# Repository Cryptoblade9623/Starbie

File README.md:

# Starbie
Motion and button controlled pet with an OLED display, humidity and temperature sensor and motion sensor.
It is controlled by an ESP32 C3 Supermini.
This is a guide, by SharKing Studios from Half-Life.
The files include the KiCad files, gerbers, drill files, firmware - which you will have to put into a folder of the same name and then open in the Arduino IDE, footprints for the custom silkscreen, non - KiCad symbols and footprints for the screen, ESP32, and DHT11, and my personal sprite creation.
I have not included the swicthes and keycaps because I have 4 switches and quite a few keycaps from previous projects.

## Instructions
1. Solder the 10K ohm resistor onto the top left corner of the board.
2. Solder the MPU6050 onto the middle area of the board with pinheaders.
3. Solder the mechanical switches into their corners on the PCB.
4. Solder on the OLED display in the middle of the board, above the MPU6050.
5. Solder the DHT11 in between the resistor and the OLED.
6. Finally solder the ESP32 onto the right side of the board so that the USBC port just hangs off the egde.
7. You can also add some small stickers onto the tips of the corners or on the back if you have them, but this is completely optional.
And you're done!

## BOM
| Name                | Purpose                                                                 | Quantity | Price | Total | Vendor     | Link                                                                                                                                                                                                                                                                                                                                                                                                                                                                                                                                                                                                                                                                                                |
|---------------------|-------------------------------------------------------------------------|----------|-------|-------|------------|-----------------------------------------------------------------------------------------------------------------------------------------------------------------------------------------------------------------------------------------------------------------------------------------------------------------------------------------------------------------------------------------------------------------------------------------------------------------------------------------------------------------------------------------------------------------------------------------------------------------------------------------------------------------------------------------------------|
| ESP32 C3 Supermini  | Control the screen and take inputs from the other parts.                | 1        | $3.05 | $3.05 | AliExpress | https://www.aliexpress.com/item/1005007869446657.html?spm=a2g0o.productlist.main.11.206e1bcdmjCEWO&algo_pvid=0b73490b-3db1-475a-b949-48b70c4bc669&algo_exp_id=0b73490b-3db1-475a-b949-48b70c4bc669-10&pdp_ext_f=%7B%22order%22%3A%22625%22%2C%22eval%22%3A%221%22%2C%22fromPage%22%3A%22search%22%7D&pdp_npi=6%40dis%21USD%213.05%211.35%21%21%213.05%211.35%21%4021038a9c17917201267658074e0e1e%2112000042625562850%21sea%21GB%210%21ABX%211%210%21n_tag%3A-29910%3Bd%3Ad6cd2d24%3Bm03_new_user%3A-29895%3BpisId%3A5000000218643706&curPageLogUid=5fYpmBZWpQCx&utparam-url=scene%3Asearch%7Cquery_from%3A%7Cx_object_id%3A1005007869446657%7C_p_origin_prod%3A                                     |
| MPU6050             | Measure when and how far the starbie moves, and the temperature.        | 1        | $6.35 | $6.35 | AliExpress | https://www.aliexpress.com/item/1005009301512511.html?spm=a2g0o.productlist.main.6.48303357KSQoac&algo_pvid=a6a14264-ed01-42b3-9622-6b7e0ab05deb&algo_exp_id=a6a14264-ed01-42b3-9622-6b7e0ab05deb-5&pdp_ext_f=%7B%22order%22%3A%22896%22%2C%22eval%22%3A%221%22%2C%22fromPage%22%3A%22search%22%7D&pdp_npi=6%40dis%21USD%216.35%211.35%21%21%2142.31%218.97%21%4021038efe17917202091956114e0e9d%2112000048670005993%21sea%21GB%210%21ABX%211%210%21n_tag%3A-29910%3Bd%3Ad6cd2d24%3Bm03_new_user%3A-29895%3BpisId%3A5000000218643719&curPageLogUid=6Pyg4t6bDySC&utparam-url=scene%3Asearch%7Cquery_from%3A%7Cx_object_id%3A1005009301512511%7C_p_origin_prod%3A                                      |
| DHT11               | Measures temperature and humidity.                                      | 1        | $1.33 | $1.33 | AliExpress | https://www.aliexpress.com/item/1005008139877691.html?spm=a2g0o.productlist.main.56.478071f3PHmWQL&algo_pvid=b0108e3c-d75b-4ddc-9645-f7381e120316&algo_exp_id=b0108e3c-d75b-4ddc-9645-f7381e120316-53&pdp_ext_f=%7B%22order%22%3A%2248%22%2C%22spu_best_type%22%3A%22price%22%2C%22eval%22%3A%221%22%2C%22fromPage%22%3A%22search%22%7D&pdp_npi=6%40dis%21USD%212.94%211.46%21%21%2119.61%219.73%21%400b0fe0e117917203029507771e0fae%2112000043957898813%21sea%21GB%210%21ABX%211%210%21n_tag%3A-29910%3Bd%3Ad6cd2d24%3Bm03_new_user%3A-29895%3BpisId%3A5000000218644952&curPageLogUid=Pg4XL4u82SU3&utparam-url=scene%3Asearch%7Cquery_from%3A%7Cx_object_id%3A1005008139877691%7C_p_origin_prod%3A |
| 0.96"" OLED Display | Show the user the character, special effects, humidity and temperature. | 1        | $2.69 | $2.69 | AliExpress | https://www.aliexpress.com/item/1005005462085489.html?spm=a2g0o.productlist.main.2.322d89ddrd7TtE&algo_pvid=498f8125-b214-45ec-ab85-9c8a85e03899&algo_exp_id=498f8125-b214-45ec-ab85-9c8a85e03899-1&pdp_ext_f=%7B%22order%22%3A%22452%22%2C%22spu_best_type%22%3A%22price%22%2C%22eval%22%3A%221%22%2C%22fromPage%22%3A%22search%22%7D&pdp_npi=6%40dis%21USD%212.69%211.35%21%21%212.69%211.35%21%4021613b2717917205198501835e102d%2112000049496537372%21sea%21GB%210%21ABX%211%210%21n_tag%3A-29910%3Bd%3Ad6cd2d24%3Bm03_new_user%3A-29895%3BpisId%3A5000000218643705&curPageLogUid=lBeDxeLcDOXl&utparam-url=scene%3Asearch%7Cquery_from%3A%7Cx_object_id%3A1005005462085489%7C_p_origin_prod%3A   |
| 10K? Resistor       | Limit the power going to the DHT11.                                     | 1        | $0.48 | $0.48 | AliExpress | https://www.aliexpress.com/item/1005004268846582.html?spm=a2g0o.productlist.main.11.7c462a0aVNMxSC&algo_pvid=5fe0ab05-7f95-40c5-b6f9-e457673b242f&algo_exp_id=5fe0ab05-7f95-40c5-b6f9-e457673b242f-40&pdp_ext_f=%7B%22order%22%3A%22228%22%2C%22eval%22%3A%221%22%2C%22fromPage%22%3A%22search%22%7D&pdp_npi=6%40dis%21USD%210.48%210.48%21%21%210.48%210.48%21%402103849717917384362504889e0ecf%2112000028578601225%21sea%21GB%210%21ABX%211%210%21n_tag%3A-29910%3Bd%3Ad6cd2d24%3Bm03_new_user%3A-29895&curPageLogUid=vm2vWDKw8xaz&utparam-url=scene%3Asearch%7Cquery_from%3A%7Cx_object_id%3A1005004268846582%7C_p_origin_prod%3A                                                                |
| PCB                 | Connect everything and hold it together (Min. 5).                       | 5        | $0.80 | $4.00 | JLCPCB     | https://cart.jlcpcb.com/shopcart/cart/                                                                                                                                                                                                                                                                                                                                                                                                                                                                                                                                                                                                                                                              |
|                     |                                                                         |          |       |       |            |                                                                                                                                                                                                                                                                                                                                                                                                                                                                                                                                                                                                                                                                                                     |
| Subtotal            | $17.90                                                                  |          |       |       |            |                                                                                                                                                                                                                                                                                                                                                                                                                                                                                                                                                                                                                                                                                                     |
| Taxes & Shipping    | $9.28                                                                   |          |       |       |            |                                                                                                                                                                                                                                                                                                                                                                                                                                                                                                                                                                                                                                                                                                     |
| Grand Total         | $27.18                                                                  |          |       |       |            |                                                                                                                                                                                                                                                                                                                                                                                                                                                                                                                                                                                                                                                                                                     |

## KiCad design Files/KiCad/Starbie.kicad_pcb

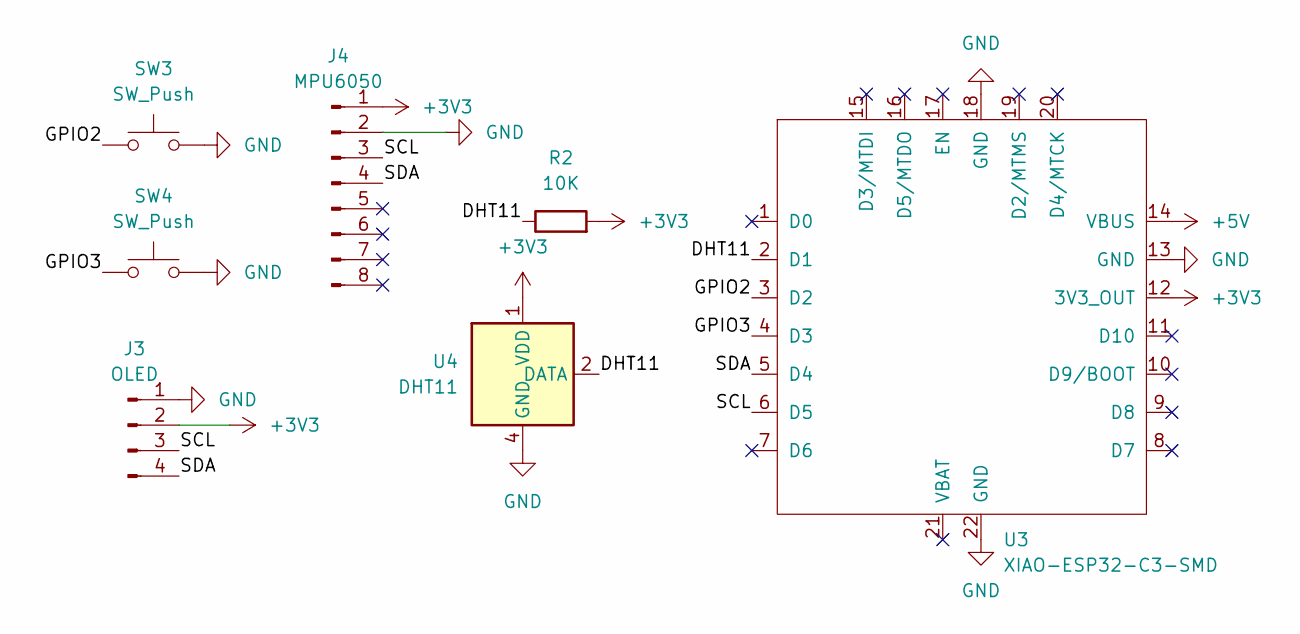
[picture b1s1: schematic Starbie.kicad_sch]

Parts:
J3: OLED; Display_128x64_096_I2C
J4: MPU6050; MPU6050_Module
R2: 10K; R_Axial_DIN0204_L3.6mm_D1.6mm_P7.62mm_Horizontal
SW3, SW4: SW_Push; SW_Cherry_MX_1.00u_PCB
U3: XIAO-ESP32-C3-SMD
U4: DHT11; Aosong_DHT11_5.5x12.0_P2.54mm

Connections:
+3V3: J3.2, J4.1, R2.2, U3.12 (3V3_OUT), U4.1 (VDD)
+5V: U3.14 (VBUS)
/DHT11: R2.1, U3.2 (D1), U4.2 (DATA)
/GPIO2: SW3.1, U3.3 (D2)
/GPIO3: SW4.1, U3.4 (D3)
/SCL: J3.3, J4.3, U3.6 (D5)
/SDA: J3.4, J4.4, U3.5 (D4)
GND: J3.1, J4.2, SW3.2, SW4.2, U3.13 (GND), U3.18 (GND), U3.22 (GND), U4.4 (GND)

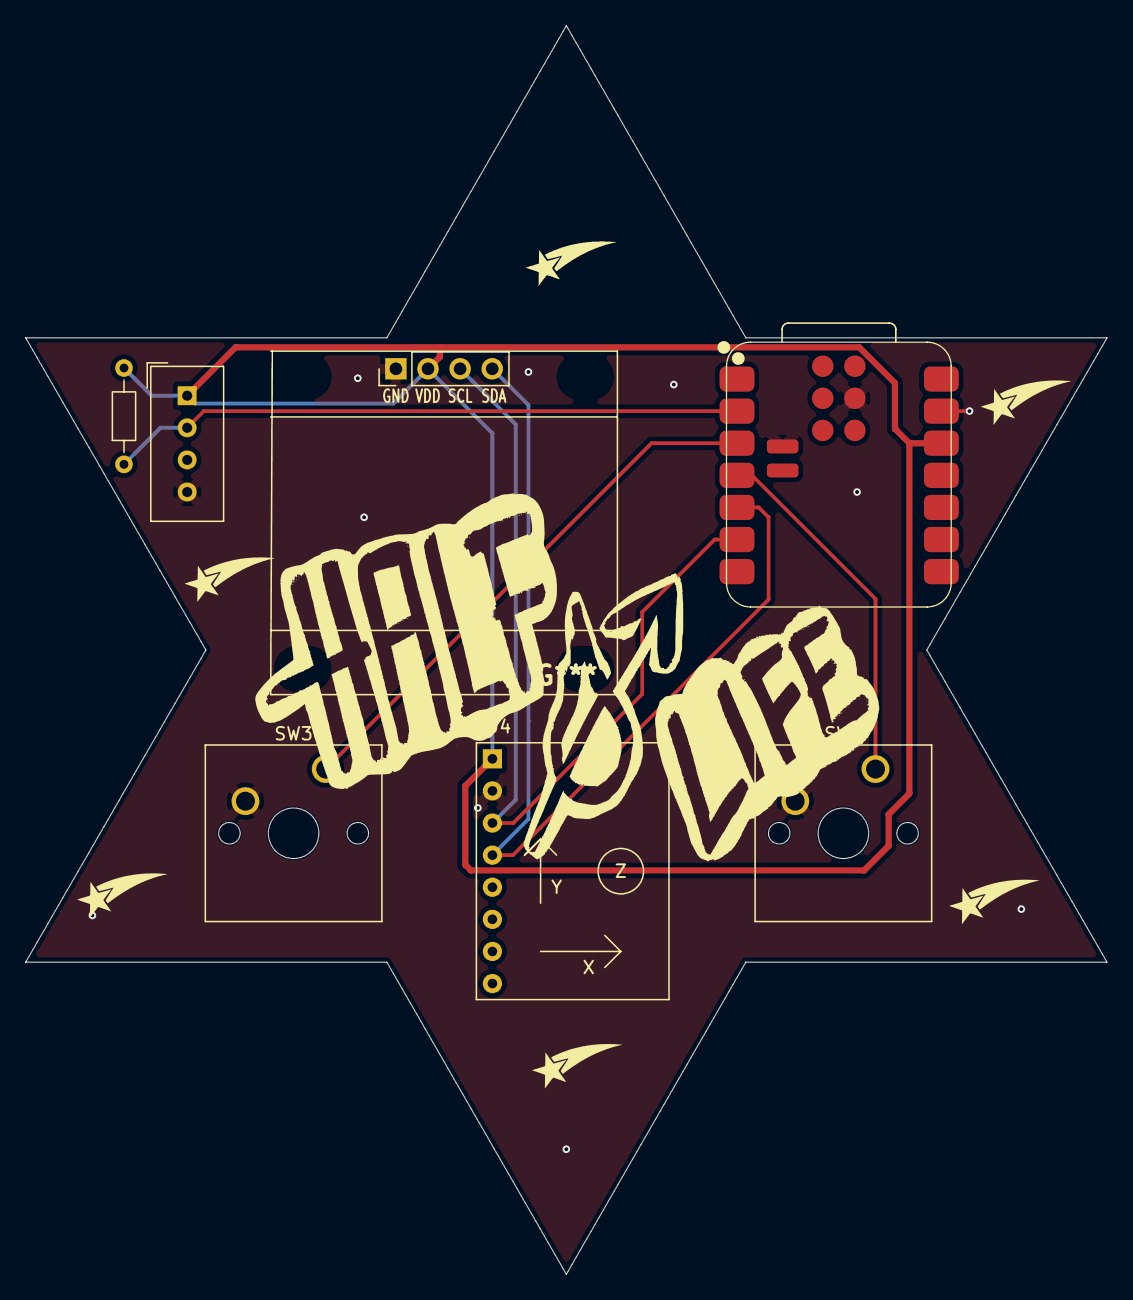
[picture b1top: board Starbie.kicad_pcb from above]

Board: 2 copper layers, 85.6 x 98.8 mm, 7 parts (0 on the bottom side), 7 nets.

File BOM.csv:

Item,Qty,Supplier,Cost/item,Total Cost,link
Xiao ESP32 C3,1,AliExpress,$6.14,$6.14,https://www.aliexpress.com/item/1005007084388623.html?spm=a2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
MPU6050,1,AliExpress,$6.35,$6.35,https://www.aliexpress.com/item/1005009301512511.html?spm=a2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
DHT11,1,AliExpress,$1.33,$1.33,https://www.aliexpress.com/item/1005008139877691.html?spm=a2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
"0.96"" OLED Display",1,AliExpress,$2.69,$2.69,https://www.aliexpress.com/item/1005005462085489.html?spm=a2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
10kΩ Resistor,1,AliExpress,$0.48,$0.48,https://www.aliexpress.com/item/1005004268846582.html?spm=a2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
PCB,5,JLCPCB,$0.80,$4.00,https://cart.jlcpcb.com/shopcart/cart/
Estimated total shipping,1,,,$9.28,
